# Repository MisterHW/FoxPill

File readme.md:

# FoxPill

an STM32L433-based, MicroPython-capable board in Arduino Nano-like form factor which adds a 128x32 px OLED display.

### Schematic

[schematic pdf](FoxPill/pdf/FoxPill-1.3_OLED_schematic.pdf)

### Board

See also

* [gerber files](FoxPill/gerber/)
* [layout pdf overview](FoxPill/pdf/FoxPill-1.3_OLED_layout.pdf)

### OtterPill

The board is derived from [OtterPill](https://github.com/Jan--Henrik/OtterPill) and backwards compatible.

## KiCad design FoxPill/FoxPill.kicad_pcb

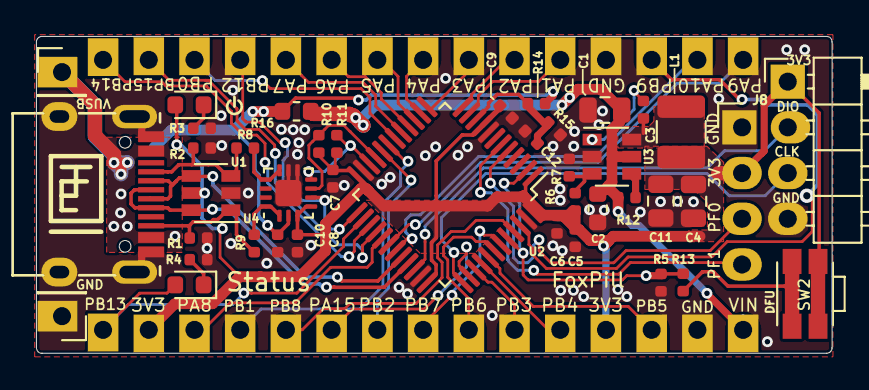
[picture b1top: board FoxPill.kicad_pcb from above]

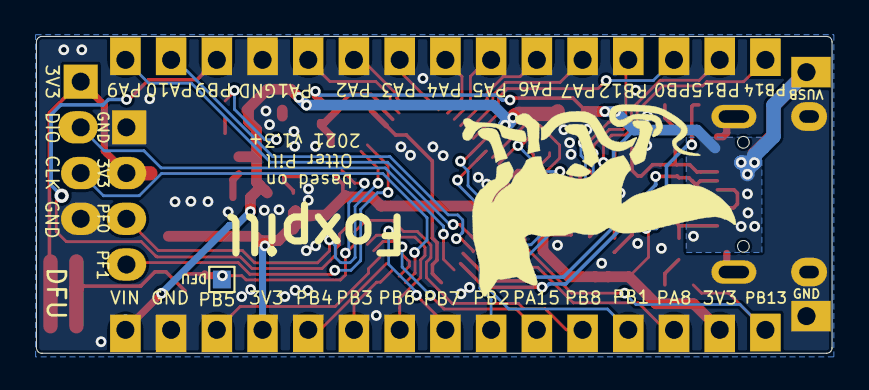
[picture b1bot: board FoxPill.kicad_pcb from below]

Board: 2 copper layers, 44.2 x 17.6 mm, 44 parts (3 on the bottom side), 50 nets.

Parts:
C1, C4, C11: 10u 25V; C_0805_2012Metric
C2: 100n 50V; C_0603_1608Metric
C3, C5, C6, C7, C8, C9, C10, C12: 100n 50V; C_0402_1005Metric
D1: LED RED; LED_0603_1608Metric
D2: LED GREEN; LED_0603_1608Metric
J1: USB-C; USB-C 16Pin
J2: VBUS; PinHeader_1x01_P2.54mm_Vertical
J3: 1; PinHeader_1x15_P2.54mm_Vertical
J4: 2; PinHeader_1x15_P2.54mm_Vertical
J5: SWD; PinHeader_1x04_P2.54mm_Horizontal
J6: GND; PinHeader_1x01_P2.54mm_Vertical
J7: PAD; TestPoint_Pad_1.0x1.0mm
J8: OLED; PinHeader_1x04_P2.54mm_Vertical
L1: 4u7; L_1210_3225Metric
R1, R2: DNP; R_0402_1005Metric
R3, R4, R5, R10, R11: 3k3; R_0402_1005Metric
R6, R12, R14: 100k; R_0402_1005Metric
R7, R15: 22k; R_0402_1005Metric
R8, R9: 0; R_0402_1005Metric
R13: 100; R_0402_1005Metric
R16: 1; R_0603_1608Metric
SW2: SW_Push; SW_SPST_EVQP7A
U1: USBLC6-4; SOT-23-6
U2: STM32F072C8Tx; LQFP-48_7x7mm_P0.5mm
U3: SY8201; SOT-23-6
U4: FUSB302BMPX; WQFN-14-1EP_2.5x2.5mm_P0.5mm_EP1.45x1.45mm

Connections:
+3V3: C4.1, C5.1, C6.1, C7.1, C8.1, C9.1, C11.1, D1.2 (A), J4.2, J4.12, J5.1, J8.2, L1.2, R6.1, R10.1, R11.1, SW2.2, U1.5 (VBUS), U2.1 (VBAT), U2.9 (VDDA), U2.24 (VDD), U2.36 (VDDIO2), U2.48 (VDD), U4.3 (VDD), U4.4 (VDD)
/BOOT0: J7.1, R5.1, R13.2, U2.2 (PC13), U2.44 (BOOT0)
CC1: J1.A5 (CC1), R2.2, R8.1, U1.3 (IO2)
CC2: J1.B5 (CC2), R1.2, R9.1, U1.1 (IO1)
GND: C1.2, C2.2, C4.2, C5.2, C6.2, C7.2, C8.2, C9.2, C10.2, C11.2, C12.2, J1.A1 (GND), J1.B1 (GND), J1.S1 (SHIELD), J3.12, J4.14, J5.4, J6.1, J8.1, R1.1, R2.1, R3.2, R4.2, R5.2, R7.2, R15.2, U1.2 (GND), U2.8 (VSSA), U2.23 (VSS), U2.35 (VSS), U2.47 (VSS), U3.2 (GND), U4.8 (GND), U4.9 (GND), U4.15 (GND)
INT_N: J3.4, U2.25 (PB12), U4.5 (INT_N)
unnamed: C3.1, U3.1 (BST)
unnamed: C3.2, L1.1, U3.6 (SW)
unnamed: D1.1 (K), R3.1
unnamed: D2.1 (K), R4.1
unnamed: R6.2, R7.1, U3.3 (FB)
unnamed: R8.2, U4.10 (CC1), U4.11 (CC1)
unnamed: R9.2, U4.1 (CC2), U4.14 (CC2)
unnamed: R12.2, U3.4 (EN)
unnamed: R13.1, SW2.1
PA0: C12.1, R14.2, R15.1, U2.10 (PA0)
PA1: J3.11, U2.11 (PA1)
PA2: J3.10, U2.12 (PA2)
PA3: J3.9, U2.13 (PA3)
PA4: J3.8, U2.14 (PA4)
PA5: J3.7, U2.15 (PA5)
PA6: J3.6, U2.16 (PA6)
PA7: J3.5, U2.17 (PA7)
PA8: J4.3, U2.29 (PA8)
PA9: J3.15, U2.30 (PA9)
PA10: J3.14, U2.31 (PA10)
PA15: J4.6, U2.38 (PA15)
PB0: J3.3, U2.18 (PB0)
PB1: J4.4, U2.19 (PB1)
PB2: J4.7, U2.20 (PB2)
PB3: J4.10, U2.39 (PB3)
PB4: J4.11, U2.40 (PB4)
PB5: J4.13, U2.41 (PB5)
PB6: J4.9, U2.42 (PB6)
PB7: J4.8, U2.43 (PB7)
PB8: J4.5, U2.45 (PB8)
PB9: J3.13, U2.46 (PB9)
PB13: D2.2 (A), J4.1, U2.26 (PB13)
PB14: J3.1, U2.27 (PB14)
PB15: J3.2, U2.28 (PB15)
PF0: J8.3, U2.5 (PF0)
PF1: J8.4, U2.6 (PF1)
SCL: R10.2, U2.21 (PB10), U4.6 (SCL)
SDA: R11.2, U2.22 (PB11), U4.7 (SDA)
SWCLK: J5.3, U2.37 (PA14)
SWDIO: J5.2, U2.34 (PA13)
USB_N: J1.A7 (D-), J1.B7 (D-), U1.4 (IO3), U2.32 (PA11)
USB_P: J1.A6 (D+), J1.B6 (D+), U1.6 (IO4), U2.33 (PA12)
VBUS: C10.1, J1.A4 (VBUS), J1.B4 (VBUS), J2.1, R14.1, R16.1, U4.2 (VBUS)
VIN: C1.1, C2.1, J4.15, R12.1, R16.2, U3.5 (VIN)

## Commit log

2021-06-13 Commit cleaned-up version with documentation.
